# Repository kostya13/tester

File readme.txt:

Звуковой тестер

Простое устройство для прозвонки электрических цепей.

Для индикации используется светодиод и звук.

Звуковой генератор собран на операционном усилителе.

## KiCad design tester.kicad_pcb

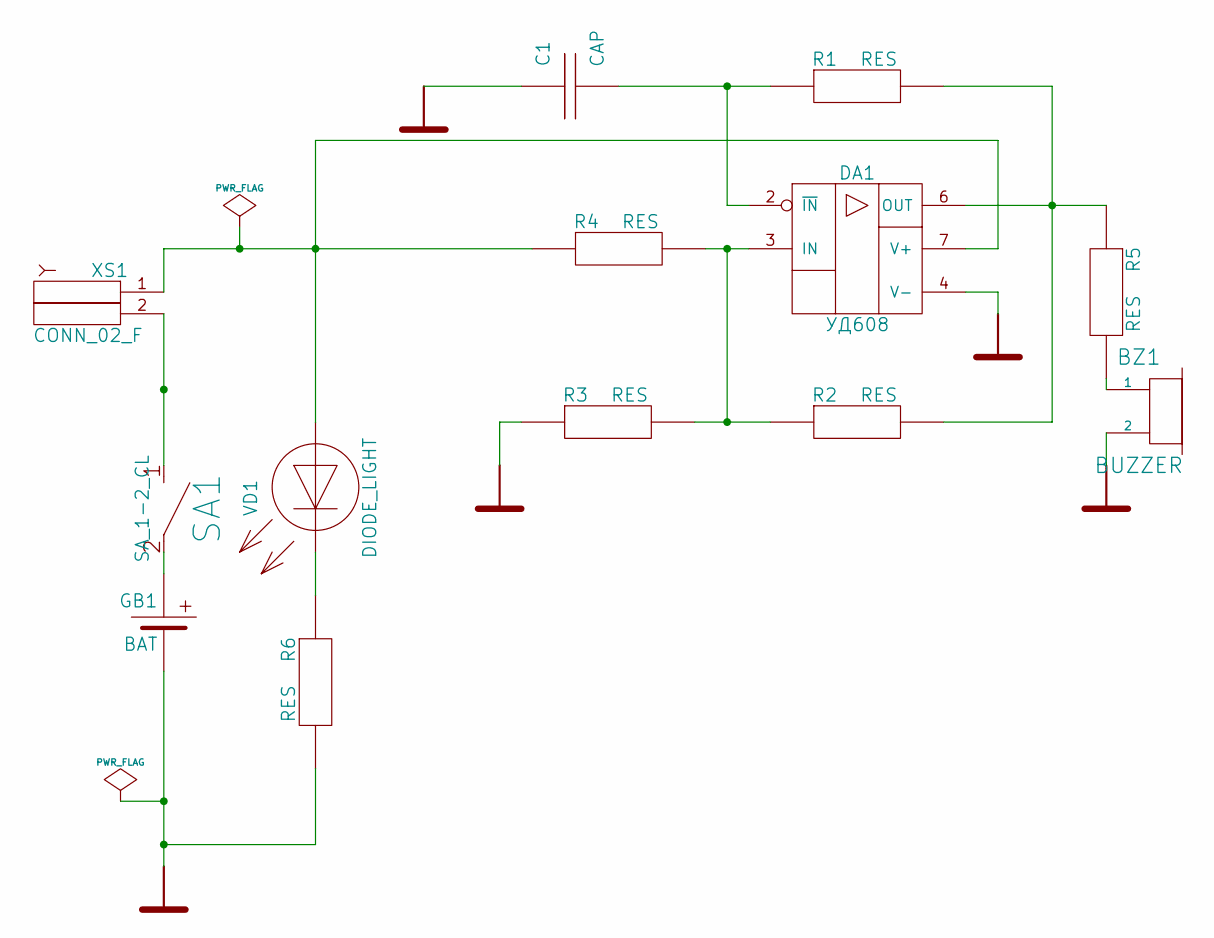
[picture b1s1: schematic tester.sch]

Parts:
BZ1: BUZZER
C1: CAP
DA1: УД608
GB1: BAT
R1, R2, R3, R4, R5, R6: RES
SA1: SA_1-2_CL
VD1: DIODE_LIGHT
XS1: CONN_02_F

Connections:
GND: BZ1.2, C1.1, DA1.4 (V-), GB1.2 (-), R3.1, R6.2
unnamed: SA1.1, XS1.2
unnamed: R6.1, VD1.2
unnamed: GB1.1 (+), SA1.2
unnamed: DA1.3 (IN), R2.1, R3.2, R4.2
unnamed: BZ1.1, R5.2
unnamed: C1.2, DA1.2 (~IN), R1.1
unnamed: DA1.7 (V+), R4.1, VD1.1, XS1.1
unnamed: DA1.6 (OUT), R1.2, R2.2, R5.1

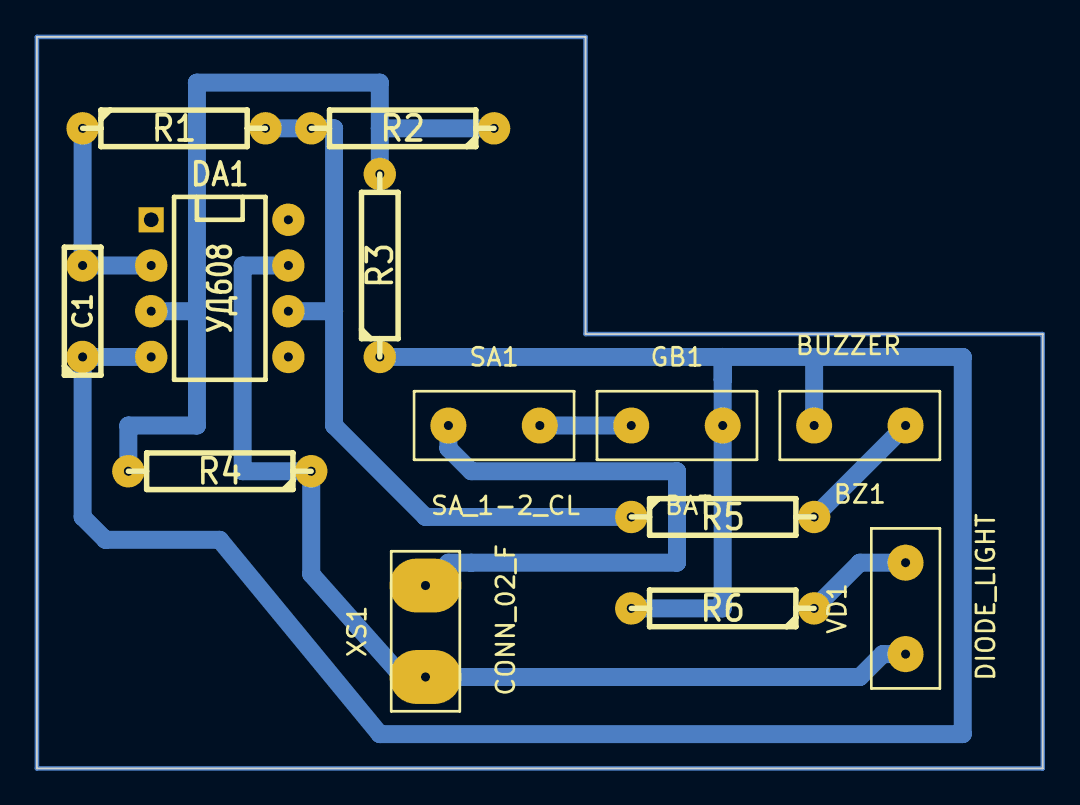
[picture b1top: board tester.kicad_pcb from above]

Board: 2 copper layers, 55.9 x 40.6 mm, 13 parts (0 on the bottom side), 9 nets.

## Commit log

2014-02-18 next step
2017-02-23 readme.txt edited online with Bitbucket
